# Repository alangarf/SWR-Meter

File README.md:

# SWR Meter

This is dumb simple SWR bridge that just outputs the forward and reflected voltages of the transmission line.

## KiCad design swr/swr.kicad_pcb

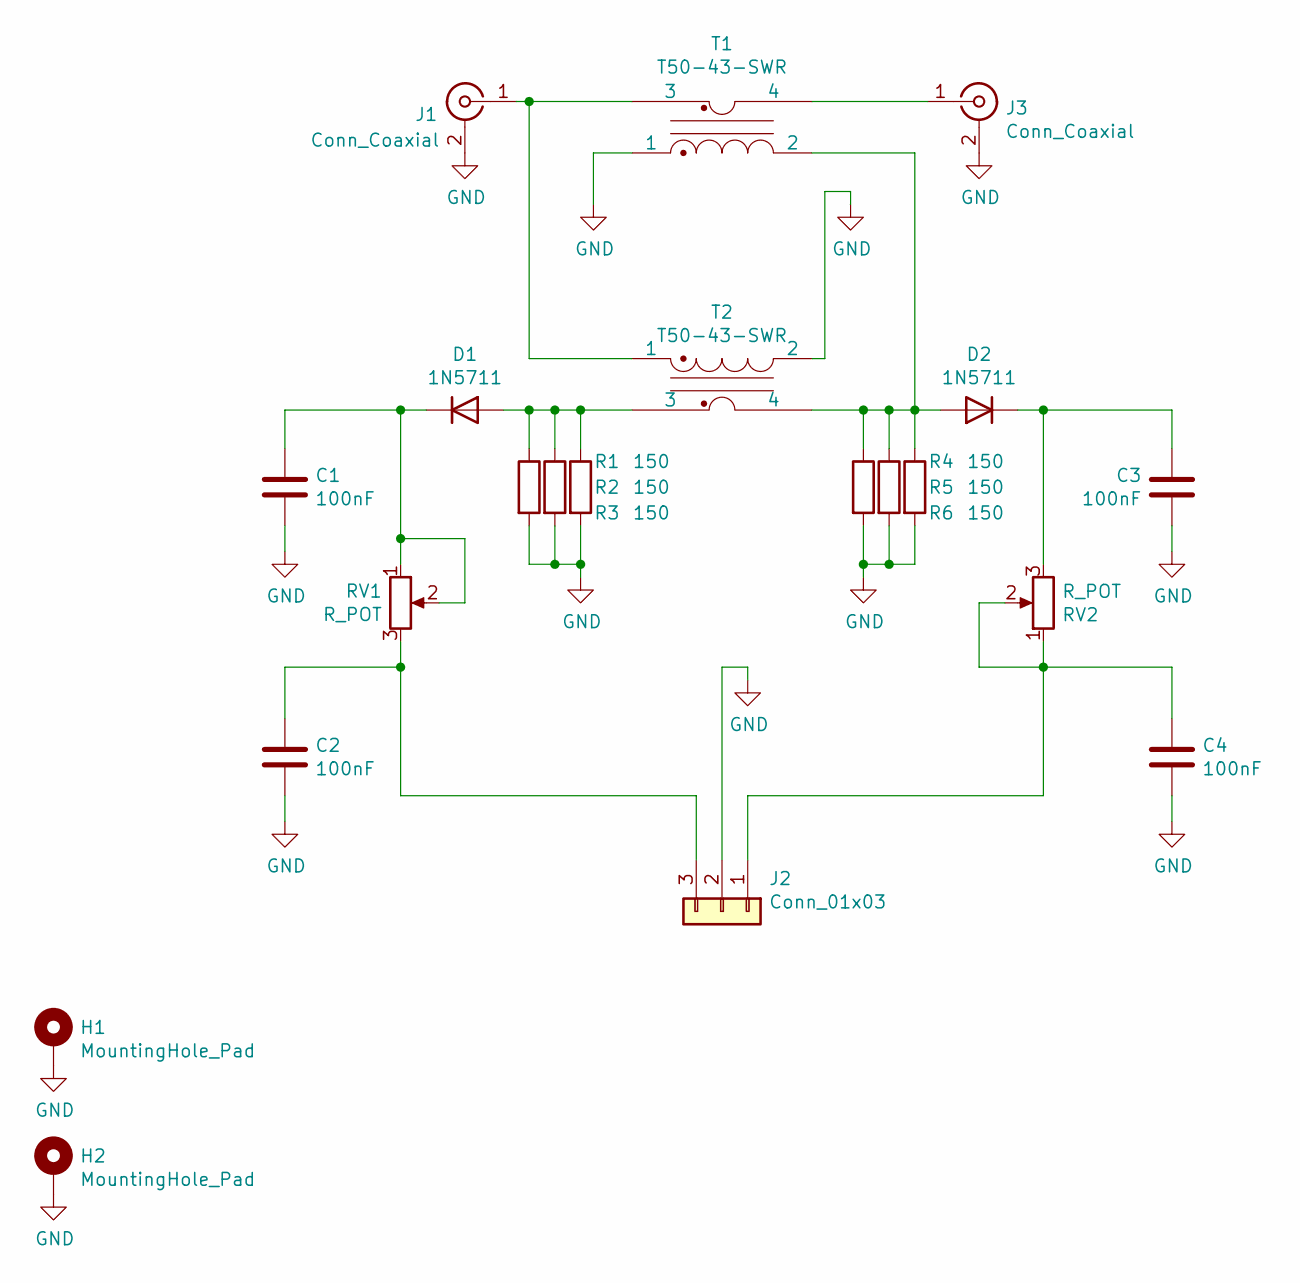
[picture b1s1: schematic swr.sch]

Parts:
C1, C2, C3, C4: 100nF; C_1206_3216Metric_Pad1.33x1.80mm_HandSolder
D1, D2: 1N5711; D_DO-35_SOD27_P7.62mm_Horizontal
H1, H2: MountingHole_Pad; MountingHole_3.2mm_M3_Pad
J1, J3: Conn_Coaxial; RF_Pads
J2: Conn_01x03; PinHeader_1x03_P2.54mm_Vertical
R1, R2, R3, R4, R5, R6: 150; R_1206_3216Metric_Pad1.30x1.75mm_HandSolder
RV1, RV2: R_POT; Potentiometer_Bourns_3296W_Vertical
T1, T2: T50-43-SWR; T50-43-swr

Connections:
GND: C1.2, C2.2, C3.2, C4.2, H1.1, H2.1, J1.2 (Ext), J2.2, J3.2 (Ext), R1.2, R2.2, R3.2, R4.2, R5.2, R6.2, T1.1, T2.2
unnamed: C1.1, D1.1 (K), RV1.1, RV1.2
unnamed: C2.1, J2.3, RV1.3
unnamed: C3.1, D2.1 (K), RV2.3
unnamed: C4.1, J2.1, RV2.1, RV2.2
unnamed: D1.2 (A), R1.1, R2.1, R3.1, T2.3
unnamed: D2.2 (A), R4.1, R5.1, R6.1, T1.2, T2.4
unnamed: J1.1 (In), T1.3, T2.1
unnamed: J3.1 (In), T1.4

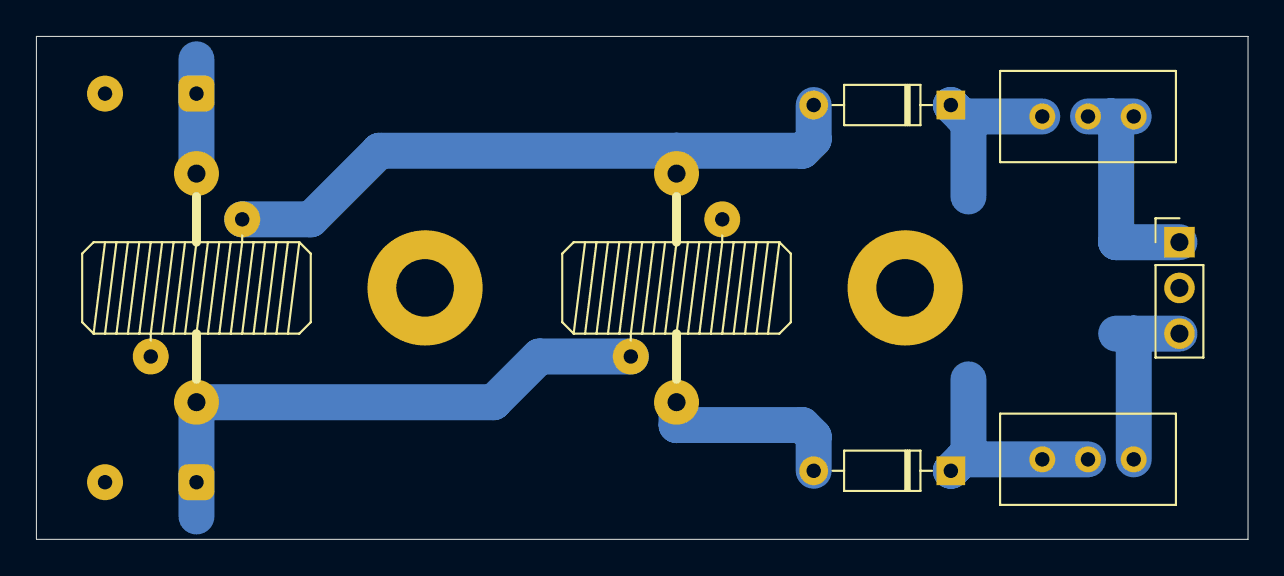
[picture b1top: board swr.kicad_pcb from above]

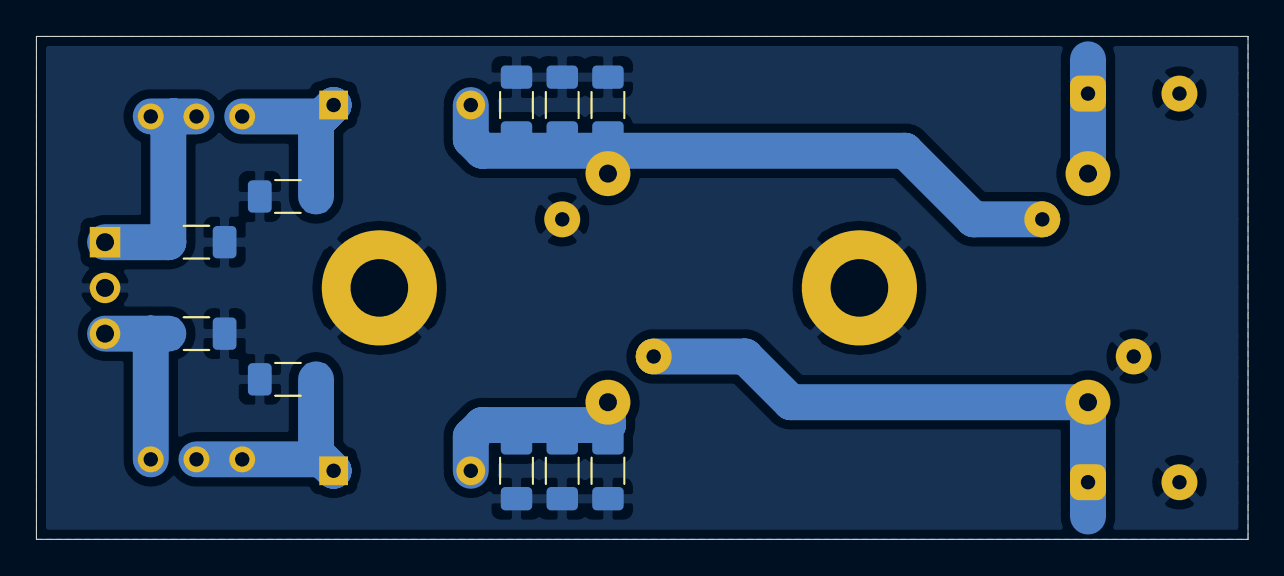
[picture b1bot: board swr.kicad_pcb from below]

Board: 2 copper layers, 67.3 x 27.9 mm, 21 parts (10 on the bottom side), 9 nets.

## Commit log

2020-10-03 Initial
2020-10-04 schema and boards added
2020-10-04 Updated library paths
